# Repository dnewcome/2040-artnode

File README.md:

# 2040-ArtNode

Open-source ArtNet LED controller built around the Raspberry Pi RP2354A. Drives four independent addressable LED universes (WS2812B / SK6812 / NeoPixel) over Ethernet using the ArtNet protocol, with integrated USB-C LiPo charging and an OLED display header.

Designed for JLCPCB turnkey assembly — all parts are from the JLCPCB/LCSC catalog with no custom stocking required.

---

## Features

- **RP2354A** dual-core Cortex-M33 / Hazard3 RISC-V @ 150MHz with 2MB flash-in-package
- **W5500** hardwired Ethernet — receives ArtNet (UDP port 6454)
- **4× serial LED outputs** — WS2812B / SK6812 via PIO state machines
- **1024 pixels** total capacity (256 pixels × 4 universes at 30fps)
- **SN74AHCT125** level shifter — 3.3V → 5V for reliable LED signal margins
- **USB-C input** with 5.1kΩ CC resistors (5V/3A profile)
- **TP4056** LiPo charger @ 500mA
- **MT3608** boost converter — battery → 5.1V system rail
- **AMS1117-3.3** LDO — 5V → 3.3V for all digital logic
- **SSD1306 OLED** I²C header (128×64, 0.96")
- **2× user buttons** + **1× reset** + **1× BOOTSEL**
- **SWD debug header**
- **100mm × 70mm**, 2-layer FR4, ENIG finish

---

## Repository Layout

```
artnet-led-controller/
├── artnet-led-controller.kicad_pro   KiCad 7 project (design rules, netclasses)
├── artnet-led-controller.kicad_sch   Schematic — all symbols inline, no library deps
├── artnet-led-controller.kicad_pcb   PCB — components placed, GND pours on both layers
├── jlcpcb-bom.csv                    BOM with LCSC part numbers for JLCPCB SMT assembly
├── gen_schematic.py                  Regenerates .kicad_sch
├── gen_pcb.py                        Regenerates .kicad_pcb
├── gen_project.py                    Regenerates .kicad_pro
├── gen_bom.py                        Regenerates jlcpcb-bom.csv
└── README.md                         Full design documentation
```

All KiCad files are generated by Python scripts. To regenerate after editing a generator:

```bash
python3 gen_schematic.py
python3 gen_pcb.py
python3 gen_project.py
python3 gen_bom.py
```

---

## Power Architecture

```
USB-C (5V/3A) ────── TP4056 (500mA) ──── Li-Ion/LiPo cell
                                                │
                                           MT3608 boost
                                                │
                                           5V system rail ──── AMS1117-3.3 ──── 3.3V rail
                                                │                                    │
                                        LED connector VCC                  RP2354A, W5500,
                                        (short strips only)                 OLED
```

LED pixel power (up to 61A at full brightness for 1024×WS2812B) must be supplied externally, directly to your LED strips. The board provides only the **control signal** and a pass-through 5V pin on each output connector for short test strips.

---

## Schematic Overview

| Ref | Part | LCSC | Function |
|-----|------|------|----------|
| U1 | RP2354A | C41378174 | MCU with 2MB flash-in-package |
| U3 | W5500 | C32646 | Ethernet TCP/IP + ArtNet |
| U4 | SN74AHCT125 | C7484 | 3.3V→5V level shifter (4ch) |
| U5 | TP4056 | C16581 | LiPo charger |
| U6 | MT3608 | C84817 | Boost converter VBAT→5V |
| U7 | AMS1117-3.3 | C6186 | 3.3V LDO |
| J1 | USB4125-GF-A | C165948 | USB-C receptacle |
| J2 | HR911105A | C12074 | RJ45 w/ integrated magnetics |
| J3 | B2B-PH-K | C131337 | JST-PH 2-pin battery |
| Y1 | 12MHz crystal | C9002 | RP2354A XOSC |
| L2 | 3.3µH inductor | C25923 | RP2354A internal buck regulator |
| Y2 | 25MHz crystal | C13738 | W5500 PHY clock |

---

## RP2354A Pin Assignment

| GPIO | Net | Function |
|------|-----|----------|
| 0–3 | LED1–4\_DATA | LED serial out → level shifter |
| 4 | I2C\_SDA | OLED |
| 5 | I2C\_SCL | OLED |
| 16 | SPI\_MISO | W5500 |
| 17 | SPI\_CS | W5500 chip select |
| 18 | SPI\_SCK | W5500 |
| 19 | SPI\_MOSI | W5500 |
| 20 | W5500\_INT | Ethernet interrupt |
| 21 | W5500\_RST | Ethernet reset |
| 22 | BTN1 | User button 1 |
| 23 | BTN2 | User button 2 |
| QSPI_SS | USB_BOOT | Hold low during reset for BOOTSEL USB/UART boot |
| QSPI | — | Internal 2MB flash-in-package |
| USB | — | Native USB (UF2 / CDC) |
| SWD | — | Debug via J10 |

---

## PCB Completion Steps

The PCB file has all components placed. To finish:

1. Open `artnet-led-controller.kicad_pcb` in KiCad 7
2. **Tools → Update PCB from Schematic** (F8) — assigns nets to pads
3. Route tracks. Critical constraints:
   - USB D+/D−: differential pair, matched length, 27Ω series resistors near J1
   - Ethernet TX/RX pairs: differential, 0.2mm/0.2mm gap
   - Crystal traces (Y1, Y2): short, GND-shielded
   - RP2354A bypass caps and internal regulator parts: within the Raspberry Pi layout guidance
4. Fill copper zones (GND on both layers already defined)
5. Run DRC — JLCPCB minimums: 0.2mm track, 0.2mm clearance, 0.3mm via drill

---

## JLCPCB Order

| Setting | Value |
|---------|-------|
| Layers | 2 |
| Thickness | 1.6mm |
| Surface finish | ENIG |
| Copper weight | 1oz |

Upload gerbers + drill file. For SMT assembly, upload `jlcpcb-bom.csv` and the pick-and-place file (**File → Fabrication Outputs → Component Placement**).

**Extended parts** (one-time setup fee each): RP2354A (C41378174), W5500, USB4125-GF-A, HR911105A.

---

## Firmware

Use an RP2350-compatible firmware stack. Recommended starting points:

- **pico-sdk** for RP2350 + W5500 driver: full control, lower overhead
- **Arduino-Pico** when RP2350 support in your selected release covers the peripherals you need
- **MicroPython** RP2350 builds plus W5500 NIC support

ArtNet reception: listen on UDP port 6454, parse `ArtDMX` packets, route universes 0–3 to GPIO 0–3 via PIO WS2812 driver.

Programming: pull `USB_BOOT` / `QSPI_SS` low during reset to enter BOOTSEL, then the RP2354A appears as a USB boot device. SWD debug via J10.

---

## License

Hardware design files released under [CERN-OHL-P v2](https://ohwr.org/cern_ohl_p_v2.txt) (permissive open hardware license).

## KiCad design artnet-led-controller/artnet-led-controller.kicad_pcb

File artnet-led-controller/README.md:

# ArtNet LED Controller

RP2354A-based ArtNet node with 4× WS2812/SK6812 serial outputs, W5500 Ethernet, USB-C LiPo charging, and SSD1306 OLED display header.

---

## Board Specifications

| Parameter | Value |
|---|---|
| MCU | Raspberry Pi RP2354A (dual-core Cortex-M33 / Hazard3 RISC-V, 150MHz) |
| Network | WIZnet W5500 hardwired TCP/IP + ArtNet (Ethernet) |
| LED outputs | 4× single-wire serial (WS2812B / SK6812 / NeoPixel compatible) |
| Max pixels | 1024 (256/universe × 4 universes at 30fps) |
| Flash | 2MB flash-in-package inside RP2354A |
| OLED | I²C header for SSD1306 128×64 |
| Buttons | 2× user + 1× reset + 1× BOOTSEL |
| Charging | TP4056 @ 500mA, USB-C input (5V/3A CC resistors) |
| Battery | Single-cell Li-Ion/LiPo via JST-PH 2-pin |
| 5V rail | MT3608 boost converter (VBAT → 5.1V) |
| 3.3V rail | AMS1117-3.3 LDO (VCC5V → 3.3V, 800mA) |
| Board | 100mm × 70mm, 2-layer FR4, ENIG |

---

## Power Architecture

```
USB-C (5V/3A) ──────────────────────────────────────────┐
                                                         │
                 ┌── TP4056 (500mA charge) ──────────────┤
                 │                                       │
Li-Ion Battery ──┘                                       │
         │                                               │
         └── MT3608 (boost → 5.1V) ── D1 (SS14) ── 5V Bus
                                                         │
                                              AMS1117-3.3 (LDO)
                                                         │
                                                      3.3V Bus
```

- When USB-C is connected: TP4056 charges the battery; boost converter runs from battery simultaneously
- When on battery only: boost converter maintains 5V rail
- D1 (Schottky) prevents USB 5V from back-feeding if simultaneously present
- LED pixel power is **external** — the board provides only the control signal and a 5V pass-through on each LED connector

> **Power budget for LED pixels:**  
> WS2812B at full white: 60mA/pixel × 1024 = 61.4A @ 5V — this **must** come from external PSUs  
> connected directly to your LED strips. The board draws ~300mA for its own electronics.

---

## Pinout — RP2354A

| GPIO | Function | Notes |
|---|---|---|
| GPIO0 | LED1_DATA | → SN74AHCT125 → 5V level |
| GPIO1 | LED2_DATA | → SN74AHCT125 → 5V level |
| GPIO2 | LED3_DATA | → SN74AHCT125 → 5V level |
| GPIO3 | LED4_DATA | → SN74AHCT125 → 5V level |
| GPIO4 | I2C0_SDA | OLED display |
| GPIO5 | I2C0_SCL | OLED display |
| GPIO16 | SPI0_MISO | W5500 |
| GPIO17 | SPI0_CS | W5500 chip select |
| GPIO18 | SPI0_SCK | W5500 |
| GPIO19 | SPI0_MOSI | W5500 |
| GPIO20 | W5500_INT | Active low interrupt |
| GPIO21 | W5500_RST | Active low reset |
| GPIO22 | BTN1 | Active low, 10k pullup |
| GPIO23 | BTN2 | Active low, 10k pullup |
| QSPI_SS | USB_BOOT | SW4 BOOTSEL, hold low during reset |
| QSPI | Internal flash | Integrated 2MB flash-in-package |
| USB | USB | Native USB (programming / serial) |
| SWCLK/SWDIO | SWD | Debug header J10 |

---

## LED Output Connectors (J5–J8)

Each connector is a 3-pin 2.54mm header:

| Pin | Signal |
|---|---|
| 1 | GND |
| 2 | DATA (5V level, from SN74AHCT125) |
| 3 | VCC5V (board 5V rail, ~300mA total available — for short LED test strips only) |

For production use with 1024 pixels, inject external 5V power directly into your LED strips and use only Pin 2 (DATA) and Pin 1 (GND) from this connector.

---

## OLED Connector (J9)

4-pin 2.54mm header:

| Pin | Signal |
|---|---|
| 1 | VCC (3.3V) |
| 2 | GND |
| 3 | SCL |
| 4 | SDA |

Compatible with common SSD1306 I²C OLED modules (128×64, 0.96").

---

## KiCad Workflow

### Opening the project

```
File → Open Project → artnet-led-controller.kicad_pro
```

The schematic (`artnet-led-controller.kicad_sch`) contains all symbols defined inline — no external library dependencies.

### Importing schematic into PCB

1. Open `artnet-led-controller.kicad_pcb`
2. **Tools → Update PCB from Schematic** (F8)
3. Click **Update PCB** — this assigns nets to all footprint pads

### Routing

The PCB has all components placed on a 100×70mm board. GND copper pours are defined on both layers. To complete routing:

```
Route → Interactive Router Settings → set to "Follow Mouse"
Route → Route All Tracks (freerouter)
```

Or use the **FreeRouting** plugin:  
`PCB Editor → Tools → External Plugins → FreeRouting`

**Recommended design rules (JLCPCB 2-layer):**

| Rule | Value |
|---|---|
| Min track width | 0.2mm |
| Min clearance | 0.2mm |
| Min via drill | 0.3mm |
| Min via pad | 0.6mm |
| Copper-to-edge | 0.3mm |

**Critical routing notes:**
- Route USB D+/D- as a matched-length differential pair, 27Ω series resistors close to USB-C connector
- Route Ethernet TX+/TX- and RX+/RX- as differential pairs (0.2mm/0.2mm gap)
- Keep 25MHz crystal traces (Y2) short and shielded with GND vias
- Keep 12MHz crystal traces (Y1) short and shielded with GND vias
- RP2354A decoupling and internal regulator parts must follow Raspberry Pi RP2350 layout guidance
- TP4056 PROG resistor (R3) must be within 10mm of the PROG pin

---

## JLCPCB Order Instructions

### Gerber export

1. **File → Fabrication Outputs → Gerbers (.gbr)**
2. Select layers: F.Cu, B.Cu, F.SilkS, B.SilkS, F.Mask, B.Mask, Edge.Cuts
3. **Fabrication Outputs → Drill Files (.drl)**

### JLCPCB order settings

| Setting | Value |
|---|---|
| Layers | 2 |
| PCB thickness | 1.6mm |
| Surface finish | ENIG (required for fine-pitch QFN/LQFP pads) |
| Copper weight | 1oz |
| Min hole size | 0.3mm |
| Solder mask | Green (or your preference) |

### SMT assembly

Upload `jlcpcb-bom.csv` and the Pick & Place file (generated from KiCad):  
**Fabrication Outputs → Component Placement (.pos)**

The BOM uses LCSC part numbers. All extended parts incur a one-time $3 setup fee per unique part number (at time of writing). The design uses:

- **Basic parts**: passives, connectors, charger, regulator, switches, crystals, level shifter
- **Extended parts**: RP2354A (C41378174), W5500 (C32646), USB4125-GF-A (C165948), HR911105A (C12074)

The RP2354A uses the QFN-60 7mm × 7mm footprint.

---

## Firmware

The RP2354A targets RP2350-compatible firmware using:

- [pico-sdk](https://github.com/raspberrypi/pico-sdk)
- [Ethernet library for Raspberry Pi Pico-class boards + W5500](https://github.com/earlephilhower/arduino-pico) when the selected release supports RP2350
- [MicroPython + W5500 nic driver](https://micropython.org) using an RP2350 build

ArtNet reception via W5500: UDP port 6454, standard ArtDMX packets.

LED protocol via PIO: RP2354A PIO state machines on GPIO0–3 for parallel WS2812B output (800kHz, single-wire).

Programming: hold SW4 BOOTSEL while pressing/releasing SW3 RESET. The RP2354A appears as a USB boot device. SWD debug via J10.

---

## Schematic Regeneration

All design files are generated by Python scripts. To regenerate:

```bash
python3 gen_project.py   # .kicad_pro
python3 gen_schematic.py # .kicad_sch  
python3 gen_pcb.py       # .kicad_pcb (component placement)
python3 gen_bom.py       # jlcpcb-bom.csv
```

---

## Design Notes

- **Integrated flash**: RP2354A contains the 2MB boot flash in-package, so U2/W25Q16JV and its QSPI routing were removed.
- **QSPI_SS / USB_BOOT**: Connected to SW4 BOOTSEL through R24 (1k). The remaining QSPI pads are left unconnected externally because they are shared with the internal flash die.
- **W5500 VDD pin**: The W5500 generates its own 1.2V core from AVDD internally. The VDD pin is an output — connect only a 100nF bypass cap (C4).
- **RP2354A core regulator**: Uses L2 (3.3µH) and C7/C9/C10 on the internal 1.1V rail, with R23/C8 filtering VREG_AVDD.
- **TP4056 TE pin**: Tied high (to VCC) to disable the safety timer — suitable when charging from USB-C which provides reliable 5V.
- **MT3608 current limit**: The 22µH inductor (L1) supports up to 2A peak. At 3.7V→5.1V the duty cycle is ~27%, continuous current ~600mA safely.

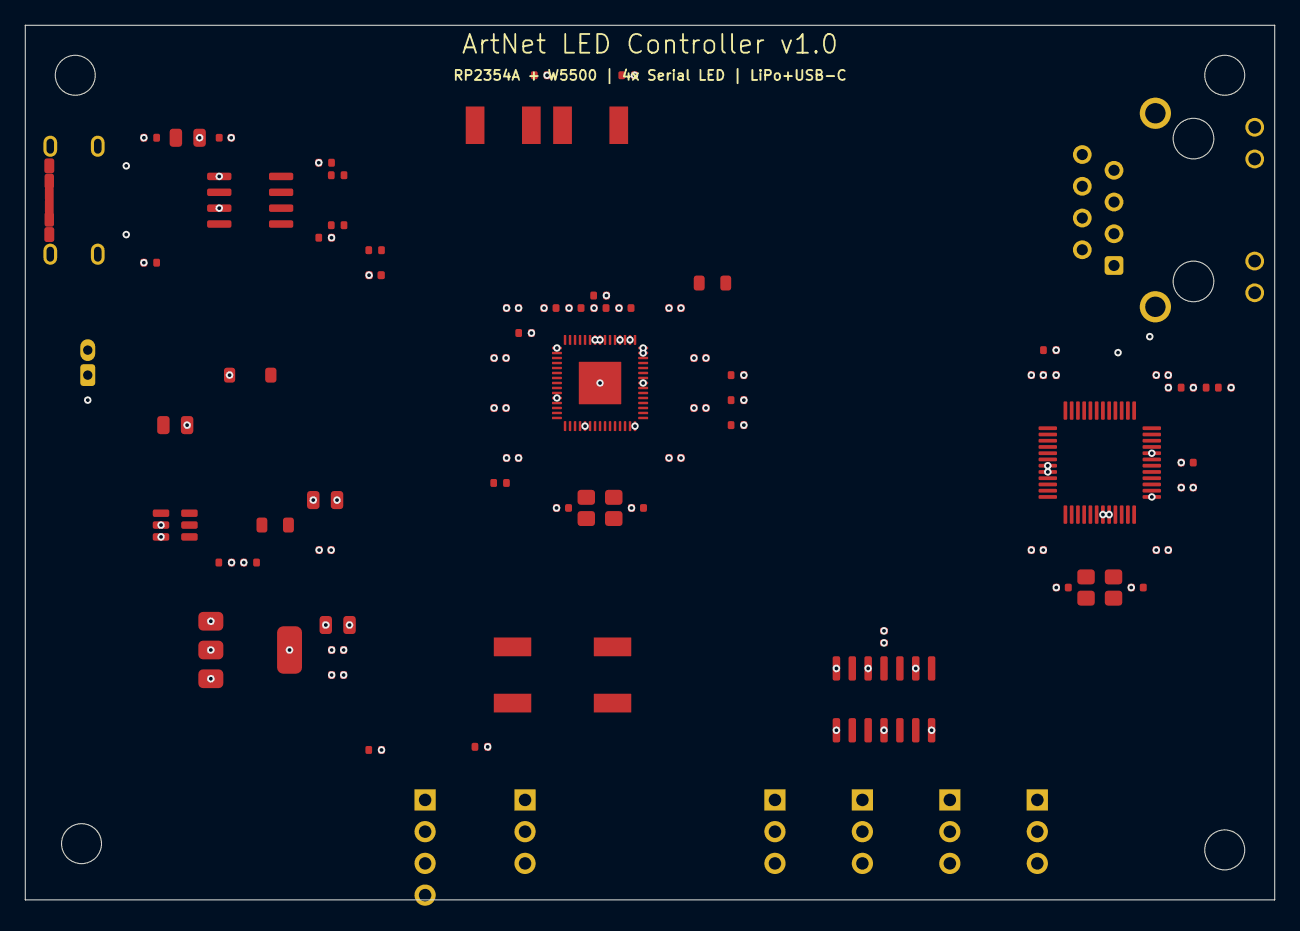
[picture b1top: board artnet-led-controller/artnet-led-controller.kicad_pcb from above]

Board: 4 copper layers, 100.0 x 70.0 mm, 84 parts (0 on the bottom side), 52 nets, no tracks yet.

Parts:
C2, C3: 12pF; C_0402_1005Metric
C4, C8, C32, C35, C37, C38, C39, C40, C41, C42, C43, C44, C45, C47, C48, C49, C50, C52: 100nF; C_0402_1005Metric
C5, C6: 18pF; C_0402_1005Metric
C7, C9, C10, C46, C51: 4.7uF; C_0402_1005Metric
C31, C33, C34, C36: 10uF; C_0805_2012Metric
D1: SS14; D_SOD-123
D2: LED_GREEN; LED_0402_1005Metric
H1, H2, H3, H4: MountingHole; MountingHole_3.2mm_M3
J1: USB4125-GF-A; USB_C_Receptacle_GCT_USB4125-xx-x_6P_TopMnt_Horizontal
J2: HR911105A; RJ45_Hanrun_HR911105A_Horizontal
J3: VBAT JST-PH-2; JST_PH_B2B-PH-K_1x02_P2.00mm_Vertical
J5: LED_OUT_1; PinHeader_1x03_P2.54mm_Vertical
J6: LED_OUT_2; PinHeader_1x03_P2.54mm_Vertical
J7: LED_OUT_3; PinHeader_1x03_P2.54mm_Vertical
J8: LED_OUT_4; PinHeader_1x03_P2.54mm_Vertical
J9: OLED_SSD1306; PinHeader_1x04_P2.54mm_Vertical
J10: SWD_DEBUG; PinHeader_1x03_P2.54mm_Vertical
L1: 22uH; L_0805_2012Metric
L2: 3.3uH; L_0805_2012Metric
R1: 750k; R_0402_1005Metric
R2: 100k; R_0402_1005Metric
R3: 2k; R_0402_1005Metric
R4, R5: 5.1k; R_0402_1005Metric
R6: 330; R_0402_1005Metric
R7, R8, R14, R15, R16, R21, R22: 10k; R_0402_1005Metric
R9, R10: 27; R_0402_1005Metric
R11, R12, R13: 12.4k; R_0402_1005Metric
R17, R18: 49.9; R_0402_1005Metric
R19, R20: 4.7k; R_0402_1005Metric
R23: 33; R_0402_1005Metric
R24: 1k; R_0402_1005Metric
SW1, SW2, SW3, SW4: SW_Push; SW_Push_1P1T_NO_CK_KSC7xxJ
U1: RP2354A; QFN-60-1EP_7x7mm_P0.4mm_EP3.4x3.4mm
U3: W5500; LQFP-48_7x7mm_P0.5mm
U4: SN74AHCT125; SOIC-14_3.9x8.7mm_P1.27mm
U5: TP4056; SOIC-8_3.9x4.9mm_P1.27mm
U6: MT3608; SOT-23-6
U7: AMS1117-3.3; SOT-223-3_TabPin2
Y1: 12MHz; Crystal_SMD_3225-4Pin_3.2x2.5mm
Y2: 25MHz; Crystal_SMD_3225-4Pin_3.2x2.5mm

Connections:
BTN1: R21.1, SW1.1, U1.34
BTN2: R22.1, SW2.1, U1.35
CHRG_STAT: D2.2, R6.2, R7.1, U5.6
ETH_CT1: J2.8, R17.1
ETH_CT2: J2.9, R18.1
ETH_TXN: J2.12, U3.12
ETH_TXP: J2.11, U3.11
GND: C2.1, C3.1, C4.1, C5.1, C6.1, C7.1, C8.1, C9.1, C10.1, C31.2, C32.2, C33.2, C34.2, C35.2, C36.2, C37.2, C38.2, C39.2, C40.2, C41.2, C42.2, C43.2, C44.2, C45.2, C46.2, C47.2, C48.2, C49.2, C50.2, C51.2, C52.2, D2.1, J1.A12, J1.B12, J2.4, J2.5, J3.2, J5.1, J6.1, J7.1, J8.1, J9.2, J10.3, R2.1, R3.1, R4.1, R5.1, R11.1, R12.1, SW1.2, SW2.2, SW3.2, SW4.2, U1.47, U1.61, U3.8, U3.32, U4.1, U4.4, U4.7, U4.9, U4.12, U5.1, U5.3, U6.2, U7.1
I2C_SCL: J9.3, R19.1, U1.8
I2C_SDA: J9.4, R20.1, U1.7
LED1_DATA_3V3: U1.2, U4.2
LED1_DATA_5V: J5.2, U4.3
LED2_DATA_3V3: U1.3, U4.5
LED2_DATA_5V: J6.2, U4.6
LED3_DATA_3V3: U1.4, U4.10
LED3_DATA_5V: J7.2, U4.8
LED4_DATA_3V3: U1.5, U4.13
LED4_DATA_5V: J8.2, U4.11
MT3608_FB: R1.1, R2.2, U6.4
MT3608_SW: L1.2, U6.5
RP_RUN: R8.1, SW3.1, U1.26
RP_XIN: C2.2, U1.21, Y1.1
RP_XOUT: C3.2, U1.22, Y1.2
SPI_CS: R15.1, U1.28, U3.24
SPI_MISO: R14.1, U1.27, U3.21
SPI_MOSI: U1.31, U3.22
SPI_SCK: U1.29, U3.23
SWCLK: J10.1, U1.24
SWDIO: J10.2, U1.25
TP4056_PROG: R3.2, U5.2
USB_BOOT: R24.2, U1.60
USB_BOOT_SW: R24.1, SW4.1
USB_CC1: J1.A5, R4.2
USB_CC2: J1.B5, R5.2
USB_DM_MCU: R10.1, U1.51
USB_DP_MCU: R9.1, U1.52
VBAT: C33.1, J3.1, U5.5, U6.1
VBOOST_RAW: D1.2, L1.1
VCC3V3: C36.1, C37.1, C38.1, C39.1, C40.1, C41.1, C42.1, C43.1, C44.1, C45.1, C46.1, C47.1, C48.1, C49.1, C50.1, C51.1, J2.7, J9.1, R7.2, R8.2, R13.2, R14.2, R15.2, R16.2, R17.2, R18.2, R19.2, R20.2, R21.2, R22.2, R23.2, U1.1, U1.11, U1.20, U1.30, U1.38, U1.44, U1.45, U1.49, U1.53, U1.54, U3.7, U3.19, U3.20, U3.25, U7.2
VCC5V: C34.1, C35.1, C52.1, D1.1, J5.3, J6.3, J7.3, J8.3, R1.2, U4.14, U6.3, U7.3
VREG_1V1: C7.2, C9.2, C10.2, L2.1, U1.6, U1.23, U1.39, U1.50
VREG_AVDD: C8.2, R23.1, U1.46
VREG_LX: L2.2, U1.48
VUSB: C31.1, C32.1, U5.4, U5.8
W5_VDD: C4.2, U3.26
W5_XTAL1: C5.2, U3.15, Y2.1
W5_XTAL2: C6.2, U3.16, Y2.2
W5500_EXRES0: R11.2, U3.10
W5500_EXRES1: R13.1, U3.5, U3.6
W5500_INT: U1.32, U3.27
W5500_RCLK: R12.2, U3.9
W5500_RST: R16.1, U1.33, U3.28

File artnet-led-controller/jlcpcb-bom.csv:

Comment,Designator,Footprint,LCSC Part #,Qty,Description,JLCPCB Part Type
RP2354A,U1,QFN-60-1EP_7x7mm_P0.4mm,C41378174,1,Dual-core Cortex-M33/RISC-V MCU with 2MB flash-in-package,Extended
W5500,U3,LQFP-48_7x7mm_P0.5mm,C32646,1,Hardwired TCP/IP Ethernet controller SPI,Extended
SN74AHCT125,U4,SOIC-14_3.9x8.7mm_P1.27mm,C7484,1,Quad buffer 3V3→5V level shifter,Basic
TP4056,U5,SOIC-8_3.9x4.9mm_P1.27mm,C16581,1,"1A Li-Ion LiPo charger, USB input",Basic
MT3608,U6,SOT-23-6,C84817,1,"2A boost converter, VBAT→5V",Basic
AMS1117-3.3,U7,SOT-223-3_TabPin2,C6186,1,1A 3.3V LDO regulator,Basic
USB4125-GF-A,J1,USB_C_Receptacle_GCT_USB4125-xx-x_6P_TopMnt_Horizontal,C165948,1,"USB-C receptacle, through-hole + SMD",Extended
HR911105A,J2,RJ45_Hanrun_HR911105A_Horizontal,C12074,1,RJ45 with integrated magnetics + LEDs,Extended
B2B-PH-K,J3,JST_PH_2pin_2mm,C131337,1,2-pin JST-PH battery connector,Basic
PinHeader_1x04,J9,PinHeader_2.54mm_1x04,C124376,1,4-pin OLED (VCC GND SCL SDA),Basic
PinHeader_1x03,"J5,J6,J7,J8",PinHeader_2.54mm_1x03,C124375,4,LED output connectors (GND DATA VCC5V),Basic
PinHeader_1x03,J10,PinHeader_2.54mm_1x03,C124375,1,SWD debug header (SWCLK SWDIO GND),Basic
12MHz 3225,Y1,Crystal_SMD_3225-4Pin,C9002,1,"12MHz crystal for RP2354A XOSC, ±30ppm",Basic
25MHz 3225,Y2,Crystal_SMD_3225-4Pin,C13738,1,"25MHz crystal for W5500 PHY, ±30ppm",Basic
22uH,L1,L_0805_2012Metric,C1046,1,22uH 2A inductor for MT3608 boost,Basic
3.3uH,L2,L_0805_2012Metric,C25923,1,RP2354A internal buck regulator inductor,Basic
750k,R1,R_0402,C25022,1,MT3608 FB divider top (Vout≈5.1V),
100k,R2,R_0402,C25741,1,MT3608 FB divider bottom,
2k,R3,R_0402,C25879,1,TP4056 PROG: sets charge current 500mA,
5.1k,"R4,R5",R_0402,C25905,2,USB-C CC1/CC2 pull-down (5V/3A sink),
330,R6,R_0402,C25104,1,Charge LED current limit,
10k,"R7,R8,R14,R15,R16,R21,R22",R_0402,C25744,7,"Pull-up: CHRG,RUN,SPI,BTN",
27,"R9,R10",R_0402,C352446,2,USB D+/D- series termination,
12.4k,"R11,R12",R_0402,C25502,2,W5500 EXRES0/RCLK per datasheet,
12.4k,R13,R_0402,C25502,1,W5500 EXRES1,
4.7k,"R19,R20",R_0402,C25900,2,I2C SDA/SCL pull-up,
49.9,"R17,R18",R_0402,C23182,2,Ethernet center-tap bias (49.9Ω),
33,R23,R_0402,C25105,1,RP2354A VREG_AVDD filter resistor,
1k,R24,R_0402,C11702,1,BOOTSEL series resistor on QSPI_SS,
100nF 0402 X5R,"C4,C8,C32,C35,C37,C38,C39,C40,C41,C42,C43,C44,C45,C47,C48,C49,C50,C52",C_0402,C14663,18,100nF 0402 bypass caps,
12pF 0402 C0G,"C2,C3",C_0402,C1525,2,12MHz crystal load caps,
18pF 0402 C0G,"C5,C6",C_0402,C1810,2,25MHz crystal load caps,
4.7uF 0402 X5R,"C7,C9,C10,C46,C51",C_0402,C19712,5,RP2354A regulator and W5500 bulk bypass,
10uF 0805 X5R,"C31,C33,C34,C36",C_0805,C19702,4,10uF bulk on all power rails,
SS14 SOD-123,D1,D_SOD-123,C2480,1,"40V/1A Schottky, power OR-ing",
LED 0402 Green,D2,LED_0402_1005Metric,C72043,1,Charge status LED (green),
KSC741J,"SW1,SW2,SW3,SW4",SW_Push_1P1T_NO_CK_KSC7xxJ,C318884,4,"Tactile switch: BTN1, BTN2, RESET, BOOTSEL",

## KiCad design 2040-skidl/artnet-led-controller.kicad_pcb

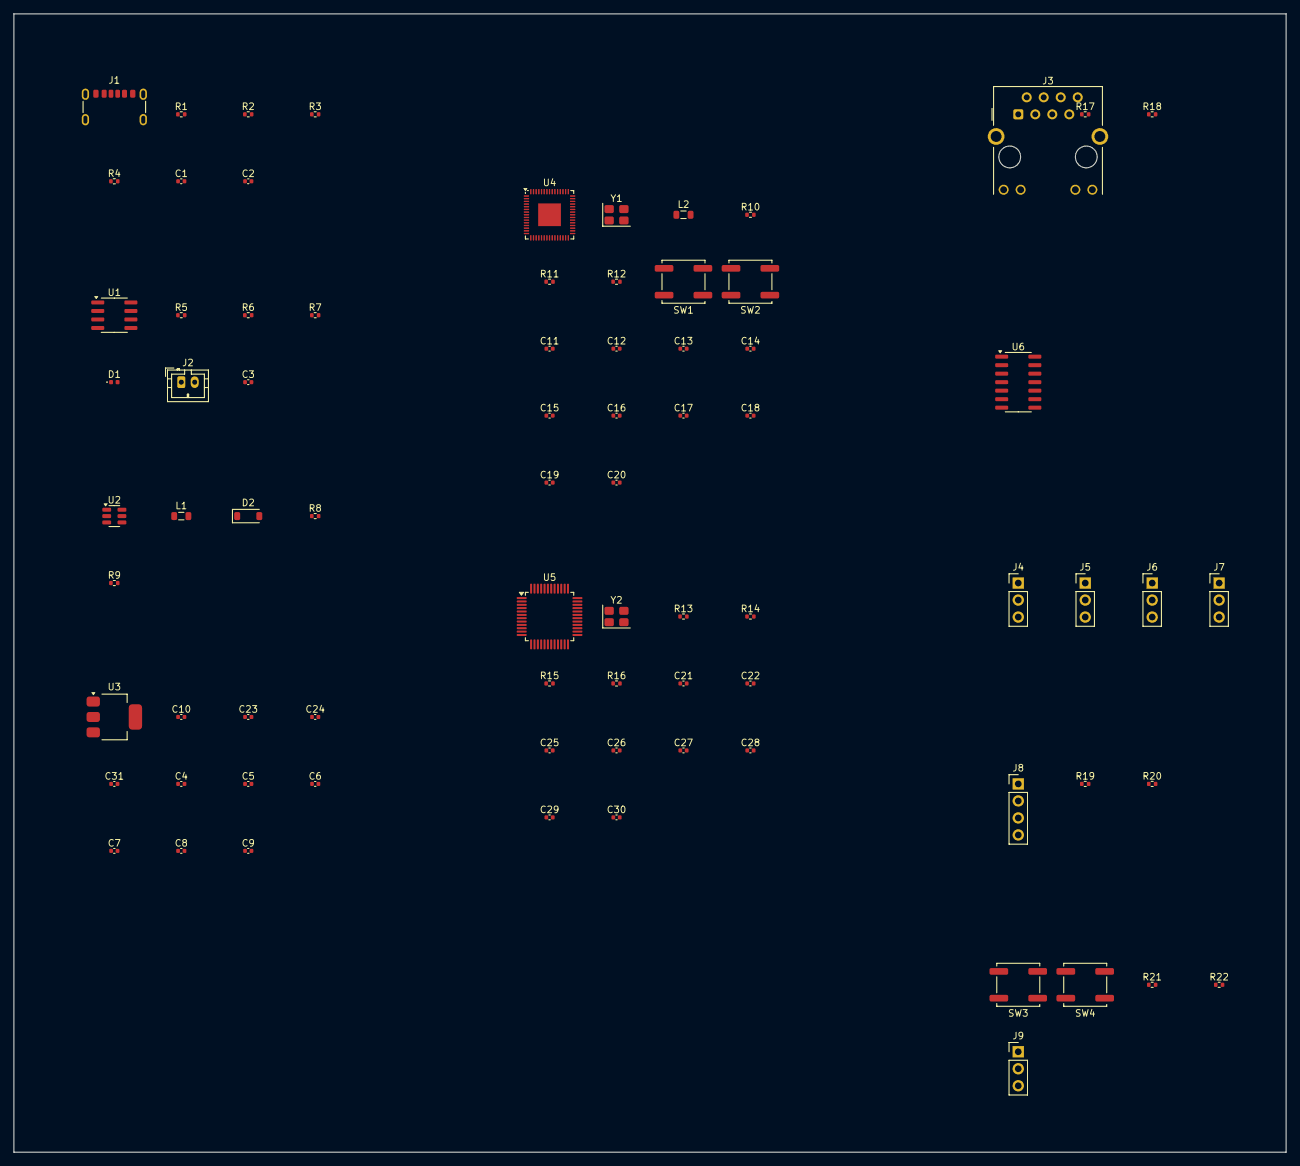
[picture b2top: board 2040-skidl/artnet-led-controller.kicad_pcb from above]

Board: 4 copper layers, 190.0 x 170.0 mm, 78 parts (0 on the bottom side), 51 nets, no tracks yet.

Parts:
C1, C3, C4, C6: 10uF; C_0402_1005Metric
C2, C5, C7, C8, C14, C15, C16, C17, C18, C19, C20, C21, C25, C26, C27, C28, C29, C31: 100nF; C_0402_1005Metric
C9, C10: 12pF; C_0402_1005Metric
C11, C12, C13, C22, C30: 4.7uF; C_0402_1005Metric
C23, C24: 18pF; C_0402_1005Metric
D1: GREEN; LED_0402_1005Metric
D2: SS14; D_SOD-123
J1: USB4125-GF-A; USB_C_Receptacle_GCT_USB4125-xx-x_6P_TopMnt_Horizontal
J2: JST-PH-2; JST_PH_B2B-PH-K_1x02_P2.00mm_Vertical
J3: HR911105A; RJ45_Hanrun_HR911105A_Horizontal
J4: LED_OUT_1; PinHeader_1x03_P2.54mm_Vertical
J5: LED_OUT_2; PinHeader_1x03_P2.54mm_Vertical
J6: LED_OUT_3; PinHeader_1x03_P2.54mm_Vertical
J7: LED_OUT_4; PinHeader_1x03_P2.54mm_Vertical
J8: OLED_SSD1306; PinHeader_1x04_P2.54mm_Vertical
J9: SWD_DEBUG; PinHeader_1x03_P2.54mm_Vertical
L1: 22uH; L_0805_2012Metric
L2: 3.3uH; L_0805_2012Metric
R1, R2: 27; R_0402_1005Metric
R3, R4: 5.1k; R_0402_1005Metric
R5: 2k; R_0402_1005Metric
R6: 330; R_0402_1005Metric
R7, R11, R14, R15, R16, R21, R22: 10k; R_0402_1005Metric
R8: 750k; R_0402_1005Metric
R9: 100k; R_0402_1005Metric
R10: 33; R_0402_1005Metric
R12: 1k; R_0402_1005Metric
R13: 12.4k; R_0402_1005Metric
R17, R18: 49.9; R_0402_1005Metric
R19, R20: 4.7k; R_0402_1005Metric
SW1: RESET; SW_Push_1P1T_NO_CK_KSC7xxJ
SW2: BOOTSEL; SW_Push_1P1T_NO_CK_KSC7xxJ
SW3: BTN1; SW_Push_1P1T_NO_CK_KSC7xxJ
SW4: BTN2; SW_Push_1P1T_NO_CK_KSC7xxJ
U1: TP4056; SOIC-8_3.9x4.9mm_P1.27mm
U2: MT3608; SOT-23-6
U3: AMS1117-3.3; SOT-223-3_TabPin2
U4: RP2354A; QFN-60-1EP_7x7mm_P0.4mm_EP3.4x3.4mm
U5: W5500; LQFP-48_7x7mm_P0.5mm
U6: SN74AHCT125; SOIC-14_3.9x8.7mm_P1.27mm
Y1: 12MHz; Crystal_SMD_3225-4Pin_3.2x2.5mm
Y2: 25MHz; Crystal_SMD_3225-4Pin_3.2x2.5mm

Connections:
BOOT_SW: R12.2, SW2.1
BTN1: R21.2, SW3.1, U4.34
BTN2: R22.2, SW4.1, U4.35
CC1: J1.A5, R3.1
CC2: J1.B5, R4.1
CHRG_STAT: D1.1, R6.1, R7.2, U1.7
CT1: J3.4, R17.2
CT2: J3.5, R18.2
ETH_RXN: J3.6, U5.5
ETH_RXP: J3.3, U5.6
ETH_TXN: J3.2, U5.1
ETH_TXP: J3.1, U5.2
EXRES1: R13.1, U5.10
FB: R8.2, R9.1, U2.3
GND: C1.2, C2.2, C3.2, C4.2, C5.2, C6.2, C7.2, C8.2, C9.2, C10.2, C11.2, C12.2, C13.2, C14.2, C15.2, C16.2, C17.2, C18.2, C19.2, C20.2, C21.2, C22.2, C23.2, C24.2, C25.2, C26.2, C27.2, C28.2, C29.2, C30.2, C31.2, D1.2, J1.A12, J1.B12, J2.2, J3.SH, J4.1, J5.1, J6.1, J7.1, J8.2, J9.3, R3.2, R4.2, R5.2, R6.2, R9.2, R13.2, SW1.2, SW2.2, SW3.2, SW4.2, U1.1, U1.3, U2.2, U3.1, U4.47, U4.61, U5.3, U5.9, U5.14, U5.16, U5.19, U5.29, U5.43, U5.44, U5.45, U5.48, U6.1, U6.4, U6.7, U6.9, U6.12
I2C_SCL: J8.3, R19.2, U4.8
I2C_SDA: J8.4, R20.2, U4.7
LED1_5V: J4.2, U6.3
LED1_DATA: U4.2, U6.2
LED2_5V: J5.2, U6.6
LED2_DATA: U4.3, U6.5
LED3_5V: J6.2, U6.8
LED3_DATA: U4.4, U6.10
LED4_5V: J7.2, U6.11
LED4_DATA: U4.5, U6.13
PROG: R5.1, U1.2
RUN: R11.2, SW1.1, U4.26
SPI_CS: R15.2, U4.28, U5.32
SPI_MISO: R14.2, U4.27, U5.34
SPI_MOSI: U4.31, U5.35
SPI_SCK: U4.29, U5.33
SW: L1.1, U2.1
SWCLK: J9.1, U4.24
SWDIO: J9.2, U4.25
USB_BOOT: R12.1, U4.60
USB_DM_MCU: R2.2, U4.51
USB_DP_MCU: R1.2, U4.52
VBAT: C3.1, J2.1, U1.5, U2.4, U2.5
VBOOST_RAW: D2.1, L1.2
VCC3V3: C6.1, C7.1, C8.1, C15.1, C16.1, C17.1, C18.1, C19.1, C20.1, C21.1, C22.1, C26.1, C27.1, C28.1, C29.1, C30.1, J8.1, R7.1, R10.1, R11.1, R14.1, R15.1, R16.1, R17.1, R18.1, R19.1, R20.1, R21.1, R22.1, U3.2, U4.1, U4.11, U4.20, U4.30, U4.38, U4.44, U4.45, U4.49, U4.53, U4.54, U5.4, U5.8, U5.11, U5.15, U5.17, U5.21
VCC5V: C4.1, C5.1, C31.1, D2.2, J4.3, J5.3, J6.3, J7.3, R8.1, U3.3, U6.14
VREG_1V1: C11.1, C12.1, C13.1, L2.2, U4.6, U4.23, U4.39, U4.50
VREG_AVDD: C14.1, R10.2, U4.46
VREG_LX: L2.1, U4.48
VUSB: C1.1, C2.1, J1.A9, J1.B9, U1.4, U1.8
W5_VDD: C25.1, U5.22, U5.28
W5500_INT: U4.32, U5.36
W5500_RST: R16.2, U4.33, U5.37
XIN: C9.1, U4.21, Y1.1
XOUT: C10.1, U4.22, Y1.2
XTAL1: C23.1, U5.30, Y2.1

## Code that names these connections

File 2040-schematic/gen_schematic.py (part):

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    lpin(6,'GPIO6','9'), lpin(7,'GPIO7','10'), lpin(8,'GPIO8','12'),
    lpin(9,'GPIO9','13'), lpin(10,'GPIO10','14'), lpin(11,'GPIO11','15'),
    lpin(12,'GPIO12','16'), lpin(13,'GPIO13','17'), lpin(14,'GPIO14','18'),
    lpin(15,'GPIO15','19'), lpin(16,'XIN','21','input'), lpin(17,'XOUT','22','output'),
    lpin(18,'USB_DP','52','bidir'), lpin(19,'USB_DM','51','bidir'),
    lpin(20,'RUN','26','input'),
    lpin(21,'SWCLK','24','input'), lpin(22,'SWDIO','25','bidir'),
    rpin(0,'GPIO16','27'), rpin(1,'GPIO17','28'), rpin(2,'GPIO18','29'),
    rpin(3,'GPIO19','31'), rpin(4,'GPIO20','32'), rpin(5,'GPIO21','33'),
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    tpin(0,'IOVDD1','1'), tpin(1,'IOVDD2','11'), tpin(2,'IOVDD3','20'),
    tpin(3,'IOVDD4','30'), tpin(4,'IOVDD5','38'), tpin(5,'IOVDD6','45'),
    tpin(6,'USB_OTP_VDD','53'), tpin(7,'QSPI_IOVDD','54'),
    tpin(8,'ADC_AVDD','44'), tpin(9,'VREG_AVDD','46'),
    tpin(10,'VREG_VIN','49'),
    bpin(0,'DVDD1','6'), bpin(1,'DVDD2','23'), bpin(2,'DVDD3','39'),
    bpin(3,'GND','61'), bpin(4,'VREG_PGND','47'),
    bpin(5,'VREG_LX','48','power_out'), bpin(6,'VREG_FB','50','input'),
]
sym, ep = build_symbol('RP2354A', rp_body, rp_pins)
lib_symbols.append(sym); all_endpoints['RP2354A'] = ep
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UX, UY = 55, 70
pwr.add_comp('USB_C_Receptacle', 'J1', 'USB4125-GF-A',
    'Connector_USB:USB_C_Receptacle_GCT_USB4125-xx-x_6P_TopMnt_Horizontal', UX, UY, 'C165948')
pwr.add_global('VUSB', *pin_xy('USB_C_Receptacle', UX, UY, 'VBUS'), shape="power_in")
pwr.add_global('VUSB', *pin_xy('USB_C_Receptacle', UX, UY, 'VBUS2'), shape="power_in")
pwr.add_power('GND', *pin_xy('USB_C_Receptacle', UX, UY, 'GND'), 270)
pwr.add_power('GND', *pin_xy('USB_C_Receptacle', UX, UY, 'GND2'), 270)
pwr.add_global('USB_DP', *pin_xy('USB_C_Receptacle', UX, UY, 'D+'))
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                  bot_is_power=True, lcsc='C25905')
pwr.add_resistor('R5', '5.1k', 25, 90, 'USB_CC2', 'GND',
                  bot_is_power=True, lcsc='C25905')
pwr.add_label('USB_CC1', *pin_xy('USB_C_Receptacle', UX, UY, 'CC1'))
pwr.add_label('USB_CC2', *pin_xy('USB_C_Receptacle', UX, UY, 'CC2'))

# USB series resistors (27 ohm)
pwr.add_note("USB Series Resistors", 90, 25)
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TX, TY = 155, 70
pwr.add_comp('TP4056', 'U5', 'TP4056',
    'Package_SO:SOIC-8_3.9x4.9mm_P1.27mm', TX, TY, 'C16581')
pwr.add_global('VUSB', *pin_xy('TP4056', TX, TY, 'VCC'), shape="power_in")
pwr.add_power('GND', *pin_xy('TP4056', TX, TY, 'GND'), 270)
pwr.add_global('VBAT', *pin_xy('TP4056', TX, TY, 'BAT'), shape="power_out")
pwr.add_label('CHRG_STAT', *pin_xy('TP4056', TX, TY, '/CHRG'))
pwr.add_label('STDBY_STAT', *pin_xy('TP4056', TX, TY, '/STDBY'))
pwr.add_power('GND', *pin_xy('TP4056', TX, TY, 'TEMP'), 270)  # NTC bypass
pwr.add_global('VUSB', *pin_xy('TP4056', TX, TY, 'TE'), shape="power_in")  # disable timer

# PROG resistor (2k for 500mA charge current)
pwr.add_resistor('R3', '2k', TX - 12, TY + 15, 'TP4056_PROG', 'GND',
                  bot_is_power=True, lcsc='C25879')
pwr.add_label('TP4056_PROG', *pin_xy('TP4056', TX, TY, 'PROG'))

# Charge LED
pwr.add_comp('LED', 'D2', 'LED_GREEN', 'LED_SMD:LED_0402_1005Metric', TX + 20, TY + 10, 'C72043')
pwr.add_label('CHRG_STAT', TX + 20, TY + 10 - 3.81)
pwr.add_power('GND', TX + 20, TY + 10 + 3.81, 270)
pwr.add_resistor('R6', '330', TX + 27, TY + 10, 'CHRG_STAT', 'GND',
                  bot_is_power=True, lcsc='C25104')
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pwr.add_global('VBAT', *pin_xy('MT3608', MX, MY, 'IN'), shape="power_in")
pwr.add_power('GND', *pin_xy('MT3608', MX, MY, 'GND'), 270)
pwr.add_global('VCC5V', *pin_xy('MT3608', MX, MY, 'EN'), shape="power_in")
pwr.add_label('MT3608_SW', *pin_xy('MT3608', MX, MY, 'SW'))
pwr.add_label('MT3608_FB', *pin_xy('MT3608', MX, MY, 'FB'))
pwr.add_nc(*pin_xy('MT3608', MX, MY, 'NC'))

# Boost inductor
pwr.add_comp('L', 'L1', '22uH', 'Inductor_SMD:L_0805_2012Metric', MX + 18, MY - 8, 'C1046')
pwr.add_label('MT3608_SW', MX + 18, MY - 8 - 4.572)
pwr.add_label('VBOOST_RAW', MX + 18, MY - 8 + 4.572)

# Boost rectifier diode
pwr.add_comp('D_Schottky', 'D1', 'SS14', 'Diode_SMD:D_SOD-123', MX + 28, MY - 8, 'C2480')
pwr.add_label('VBOOST_RAW', MX + 28, MY - 8 - 3.81)
pwr.add_global('VCC5V', MX + 28, MY - 8 + 3.81, shape="power_out")

# Feedback divider
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# GPIO → global labels for inter-sheet connections
for i, gpio in enumerate(['GPIO0', 'GPIO1', 'GPIO2', 'GPIO3']):
    mcu.add_global(f'LED{i+1}_DATA_3V3', *pin_xy('RP2354A', RX, RY, gpio))
mcu.add_global('I2C_SDA', *pin_xy('RP2354A', RX, RY, 'GPIO4'))
mcu.add_global('I2C_SCL', *pin_xy('RP2354A', RX, RY, 'GPIO5'))

# SPI for W5500
mcu.add_global('SPI_MISO', *pin_xy('RP2354A', RX, RY, 'GPIO16'))
mcu.add_global('SPI_CS', *pin_xy('RP2354A', RX, RY, 'GPIO17'))
mcu.add_global('SPI_SCK', *pin_xy('RP2354A', RX, RY, 'GPIO18'))
mcu.add_global('SPI_MOSI', *pin_xy('RP2354A', RX, RY, 'GPIO19'))
mcu.add_global('W5500_INT', *pin_xy('RP2354A', RX, RY, 'GPIO20'))
mcu.add_global('W5500_RST', *pin_xy('RP2354A', RX, RY, 'GPIO21'))

# Buttons
mcu.add_global('BTN1', *pin_xy('RP2354A', RX, RY, 'GPIO22'))
mcu.add_global('BTN2', *pin_xy('RP2354A', RX, RY, 'GPIO23'))

# Unused GPIOs
for g in ['GPIO6','GPIO7','GPIO8','GPIO9','GPIO10','GPIO11','GPIO12','GPIO13',
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    mcu.add_nc(*pin_xy('RP2354A', RX, RY, g))

# QSPI (internal flash, leave external pads NC except SS=USB_BOOT)
mcu.add_global('USB_BOOT', *pin_xy('RP2354A', RX, RY, 'QSPI_SS'))
for qpin in ['QSPI_SCLK','QSPI_SD0','QSPI_SD1','QSPI_SD2','QSPI_SD3']:
    mcu.add_nc(*pin_xy('RP2354A', RX, RY, qpin))

# USB
mcu.add_global('USB_DP_MCU', *pin_xy('RP2354A', RX, RY, 'USB_DP'))
mcu.add_global('USB_DM_MCU', *pin_xy('RP2354A', RX, RY, 'USB_DM'))

# Crystal
mcu.add_label('RP_XIN', *pin_xy('RP2354A', RX, RY, 'XIN'))
mcu.add_label('RP_XOUT', *pin_xy('RP2354A', RX, RY, 'XOUT'))

# RUN, SWD
mcu.add_global('RP_RUN', *pin_xy('RP2354A', RX, RY, 'RUN'))
mcu.add_global('SWCLK', *pin_xy('RP2354A', RX, RY, 'SWCLK'))
mcu.add_global('SWDIO', *pin_xy('RP2354A', RX, RY, 'SWDIO'))

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mcu.add_power('GND', *pin_xy('RP2354A', RX, RY, 'VREG_PGND'), 270)

# Core regulator
mcu.add_label('VREG_LX', *pin_xy('RP2354A', RX, RY, 'VREG_LX'))
mcu.add_label('VREG_1V1', *pin_xy('RP2354A', RX, RY, 'VREG_FB'))
for p in ['DVDD1', 'DVDD2', 'DVDD3']:
    mcu.add_label('VREG_1V1', *pin_xy('RP2354A', RX, RY, p))
mcu.add_label('VREG_AVDD', *pin_xy('RP2354A', RX, RY, 'VREG_AVDD'))

# VREG inductor
mcu.add_comp('L', 'L2', '3.3uH', 'Inductor_SMD:L_0805_2012Metric', RX + 30, RY + 40, 'C25923')
mcu.add_label('VREG_LX', RX + 30, RY + 40 - 4.572)
mcu.add_label('VREG_1V1', RX + 30, RY + 40 + 4.572)

# VREG_AVDD filter resistor
mcu.add_resistor('R23', '33', RX + 40, RY + 30, 'VCC3V3', 'VREG_AVDD',
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YX, YY = RX - 45, RY - 50
mcu.add_comp('Crystal', 'Y1', '12MHz',
    'Crystal:Crystal_SMD_3225-4Pin_3.2x2.5mm', YX, YY, 'C9002')
mcu.add_label('RP_XIN', *pin_xy('Crystal', YX, YY, 'XIN'))
mcu.add_label('RP_XOUT', *pin_xy('Crystal', YX, YY, 'XOUT'))
mcu.add_cap('C2', '12pF', YX - 10, YY, 'RP_XIN', lcsc='C1525')
mcu.add_cap('C3', '12pF', YX + 10, YY, 'RP_XOUT', lcsc='C1525')

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                  top_is_power=True, bot_is_global=True, lcsc='C25744')
mcu.add_comp('SW_Push', 'SW3', 'RESET',
    'Button_Switch_SMD:SW_Push_1P1T_NO_CK_KSC7xxJ', RX - 70, RY + 20, 'C318884')
mcu.add_global('RP_RUN', *pin_xy('SW_Push', RX - 70, RY + 20, 'A'))
mcu.add_power('GND', *pin_xy('SW_Push', RX - 70, RY + 20, 'B'), 270)

# Boot button
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                  top_is_global=True, lcsc='C11702')
mcu.add_comp('SW_Push', 'SW4', 'BOOTSEL',
    'Button_Switch_SMD:SW_Push_1P1T_NO_CK_KSC7xxJ', RX - 70, RY + 35, 'C318884')
mcu.add_label('USB_BOOT_SW', *pin_xy('SW_Push', RX - 70, RY + 35, 'A'))
mcu.add_power('GND', *pin_xy('SW_Push', RX - 70, RY + 35, 'B'), 270)


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    'Package_QFP:LQFP-48_7x7mm_P0.5mm', WX, WY, 'C32646')

# SPI
eth.add_global('SPI_MISO', *pin_xy('W5500', WX, WY, 'MISO'))
eth.add_global('SPI_MOSI', *pin_xy('W5500', WX, WY, 'MOSI'))
eth.add_global('SPI_SCK', *pin_xy('W5500', WX, WY, 'SCLK'))
eth.add_global('SPI_CS', *pin_xy('W5500', WX, WY, '/SCSn'))
eth.add_global('W5500_INT', *pin_xy('W5500', WX, WY, '/INTn'))
eth.add_global('W5500_RST', *pin_xy('W5500', WX, WY, '/RSTn'))

# PHY
eth.add_label('ETH_TXP', *pin_xy('W5500', WX, WY, 'TXP'))
eth.add_label('ETH_TXN', *pin_xy('W5500', WX, WY, 'TXN'))
eth.add_label('ETH_RXP', *pin_xy('W5500', WX, WY, 'RXP'))
eth.add_label('ETH_RXN', *pin_xy('W5500', WX, WY, 'RXN'))

# Crystal
eth.add_label('W5_XTAL1', *pin_xy('W5500', WX, WY, 'XTAL1'))
eth.add_label('W5_XTAL2', *pin_xy('W5500', WX, WY, 'XTAL2'))

# EXRES/RCLK
eth.add_label('W5500_EXRES0', *pin_xy('W5500', WX, WY, 'EXRES0'))
eth.add_label('W5500_RCLK', *pin_xy('W5500', WX, WY, 'RCLK'))
eth.add_label('W5500_EXRES1', *pin_xy('W5500', WX, WY, 'EXRES1'))
eth.add_label('W5500_EXRES1', *pin_xy('W5500', WX, WY, 'AVCCRST'))

# Power
for p in ['VDDIO', 'AVDD', 'AVDD2', 'VDDIO2']:
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    eth.add_power('GND', *pin_xy('W5500', WX, WY, p), 270)

# VDD (internal 1.1V)
eth.add_label('W5_VDD', *pin_xy('W5500', WX, WY, 'VDD'))
eth.add_cap('C4', '100nF', WX - 10, WY - 25, 'W5_VDD')

# RSVD pins
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Y2X, Y2Y = WX + 70, WY - 40
eth.add_comp('Crystal', 'Y2', '25MHz',
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
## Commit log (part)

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2026-04-14 Redesign controller around RP2354A
2026-04-14 Clean PCB DRC and rotate RJ45
